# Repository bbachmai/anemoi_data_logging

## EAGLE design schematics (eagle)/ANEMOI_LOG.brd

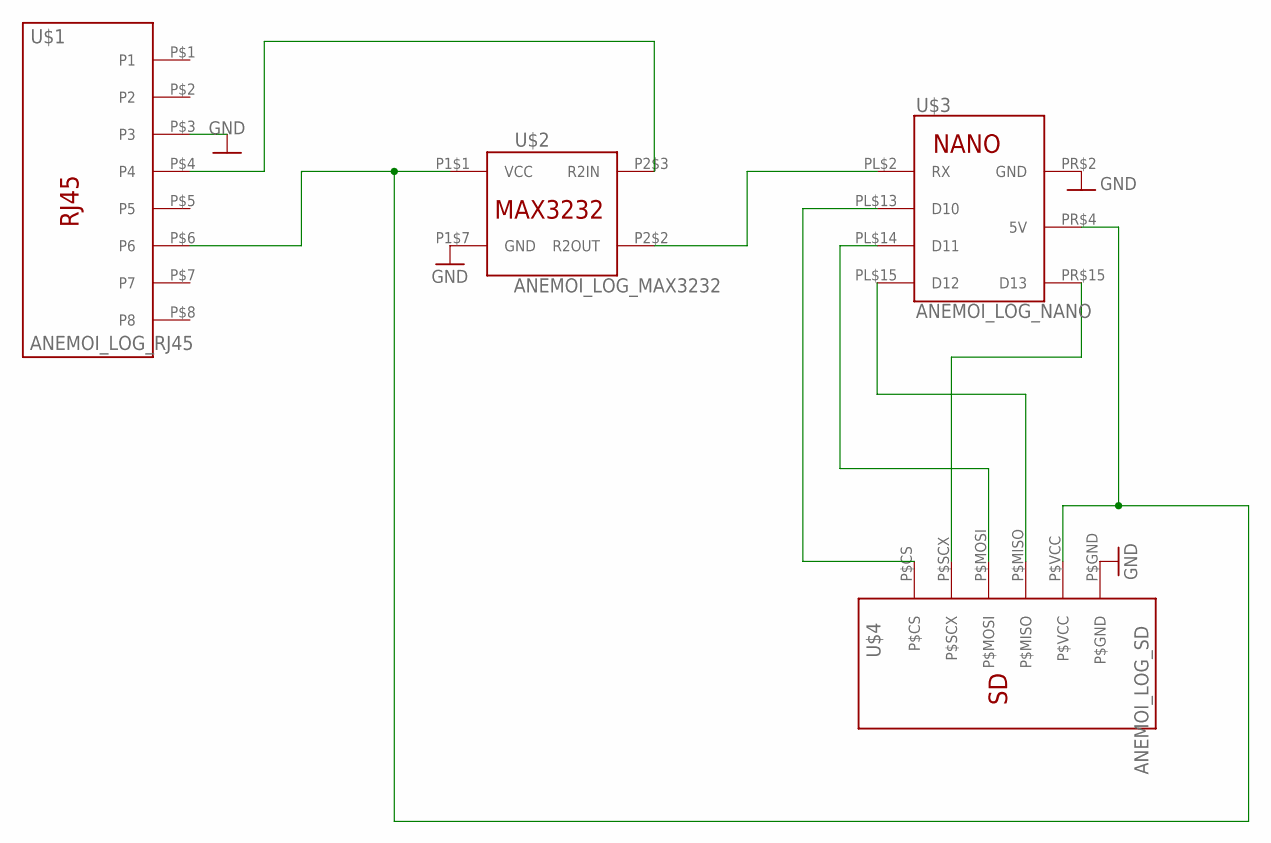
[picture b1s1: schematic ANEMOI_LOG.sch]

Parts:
U$1: ANEMOI_LOG_RJ45
U$2: ANEMOI_LOG_MAX3232; ANEMOI_LOG_MAX2323
U$3: ANEMOI_LOG_NANO
U$4: ANEMOI_LOG_SD

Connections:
5V: U$1.P$6 (P6), U$2.P1$1 (VCC), U$3.PR$4 (5V), U$4.P$VCC
CS: U$3.PL$13 (D10), U$4.P$CS
GND: U$1.P$3 (P3), U$2.P1$7 (GND), U$3.PR$2 (GND), U$4.P$GND
MISO: U$3.PL$15 (D12), U$4.P$MISO
MOSI: U$3.PL$14 (D11), U$4.P$MOSI
RX: U$1.P$4 (P4), U$2.P2$3 (R2IN)
RX2: U$2.P2$2 (R2OUT), U$3.PL$2 (RX)
SCX: U$3.PR$15 (D13), U$4.P$SCX

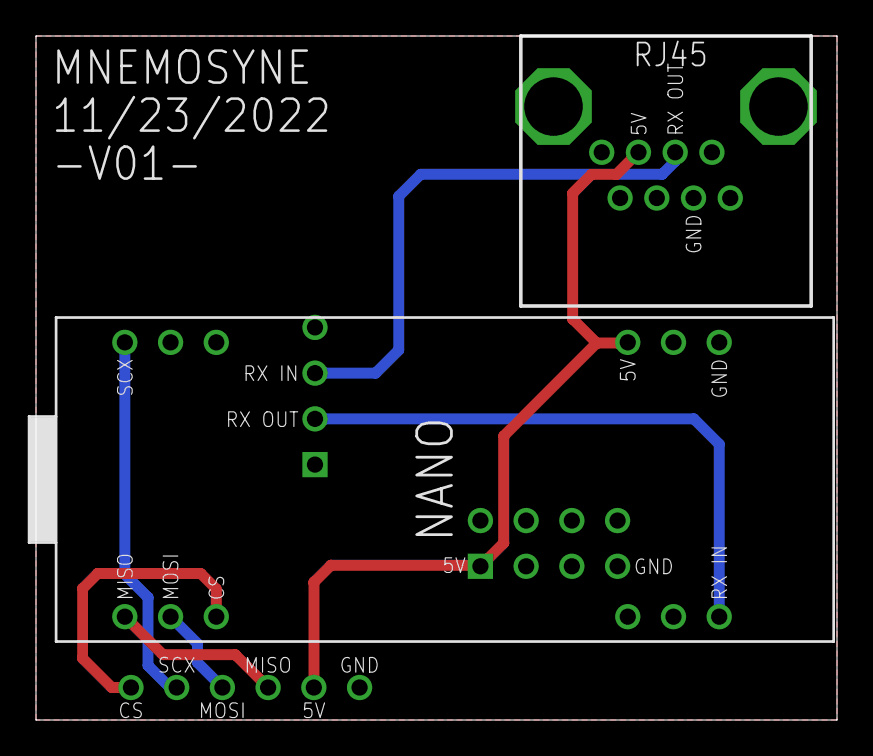
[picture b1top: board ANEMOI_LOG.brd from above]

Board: 2 copper layers, 44.5 x 38.0 mm, 4 parts (1 on the bottom side), 8 nets.

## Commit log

2024-01-20 Initial commit of log decoding repo
2024-01-20 folder structure updated
2024-01-20 Added arduino logging code and schematics
